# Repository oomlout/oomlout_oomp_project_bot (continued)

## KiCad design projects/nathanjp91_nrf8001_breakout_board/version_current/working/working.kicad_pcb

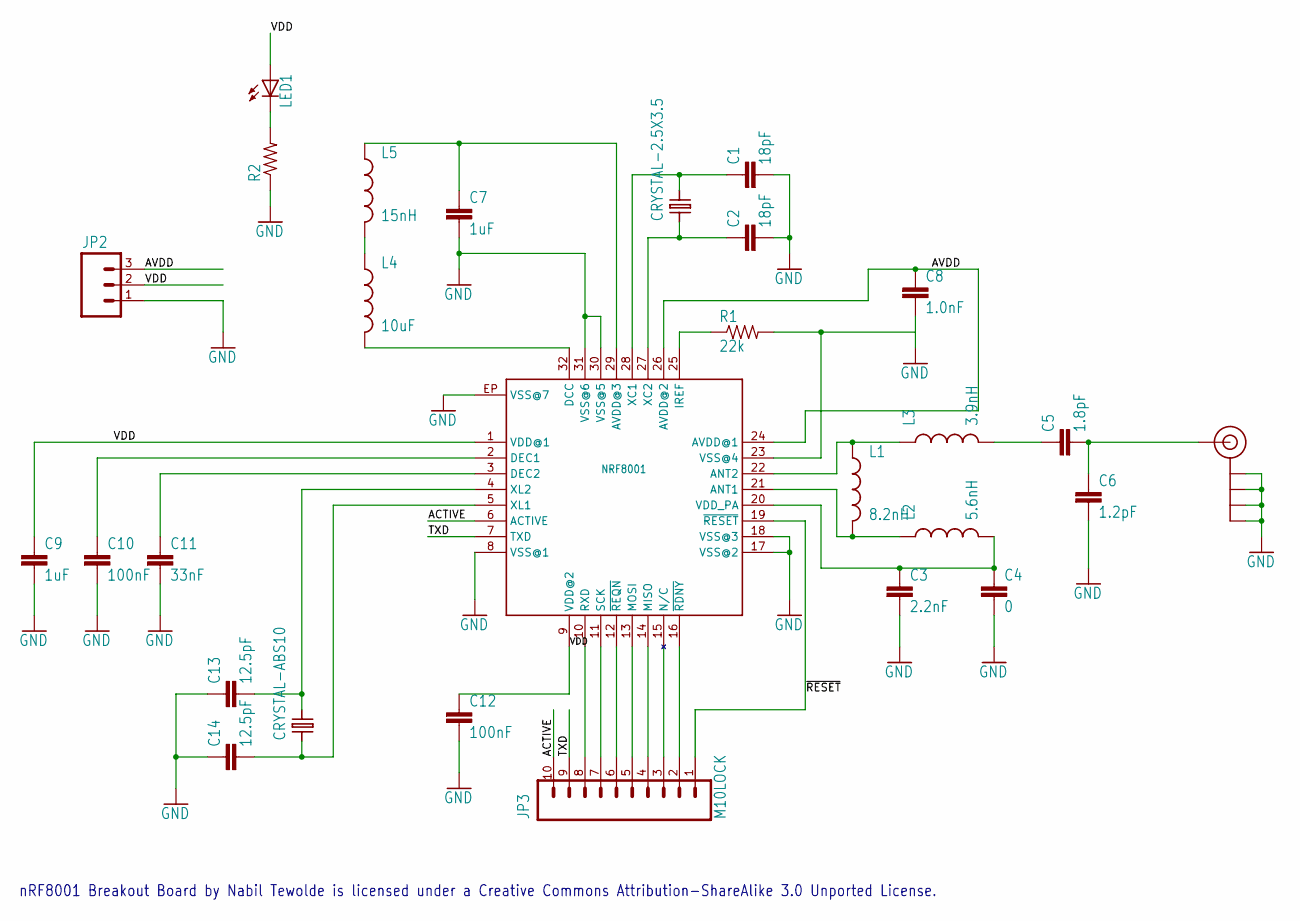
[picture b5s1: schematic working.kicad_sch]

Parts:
C1, C2: 18pF; 0603-CAP
C3: 2.2nF; 0603-CAP
C4: 0; 0603-CAP
C5: 1.8pF; 0603-CAP
C6: 1.2pF; 0603-CAP
C7, C9: 1uF; 0603-CAP
C8: 1.0nF; 0603-CAP
C10, C12: 100nF; 0603-CAP
C11: 33nF; 0603-CAP
C13, C14: 12.5pF; 0603-CAP
J$1: SMA_EDGE; SMA-EDGE
JP2: M03LOCK; 1X03_LOCK
JP3: M10LOCK; 1X10_LOCK
L1: 8.2nH; 0603
L2: 5.6nH; 0603
L3: 3.9nH; 0603
L4: 10uF; 0603
L5: 15nH; 0603
LED1: LED0603; LED-0603
R1: 22k; 0603-RES
R2: RESISTOR0603-RES; 0603-RES
U1: NRF8001; QFN-32
X1: CRYSTAL-2.5X3.5
X2: CRYSTAL-ABS10

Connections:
ACTIVE: JP3.10, U1.6 (ACTIVE)
AVDD: C8.1, JP2.3, U1.24 (AVDD@1), U1.26 (AVDD@2)
unnamed: L4.1, L5.2
unnamed: L4.2, U1.32 (DCC)
unnamed: L1.1, L3.1, U1.22 (ANT2)
unnamed: C7.1, L5.1, U1.29 (AVDD@3)
unnamed: LED1.C, R2.2
unnamed: C10.1, U1.2 (DEC1)
unnamed: C11.1, U1.3 (DEC2)
unnamed: L1.2, L2.1, U1.21 (ANT1)
unnamed: C5.1, L3.2
unnamed: C5.2, C6.1, J$1.SIG (SIGNAL)
unnamed: R1.1, U1.25 (IREF)
unnamed: C3.1, C4.1, L2.2, U1.20 (VDD_PA)
unnamed: C2.1, U1.27 (XC2), X1.P$1
unnamed: C1.1, U1.28 (XC1), X1.P$3
unnamed: C13.2, U1.4 (XL2), X2.P$2
unnamed: C14.2, U1.5 (XL1), X2.P$1
unnamed: JP3.2, U1.16 (~RDNY)
unnamed: JP3.3, U1.15 (N/C)
unnamed: JP3.4, U1.14 (MISO)
unnamed: JP3.5, U1.13 (MOSI)
unnamed: JP3.6, U1.12 (~REQN)
unnamed: JP3.7, U1.11 (SCK)
unnamed: JP3.8, U1.10 (RXD)
TXD: JP3.9, U1.7 (TXD)
VDD: C9.1, C12.1, JP2.2, LED1.A, U1.1 (VDD@1), U1.9 (VDD@2)
~RESET: JP3.1, U1.19 (~RESET)

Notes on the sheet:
nRF8001 Breakout Board by Nabil Tewolde is licensed under a Creative Commons Attribution-ShareAlike 3.0 Unported License.

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
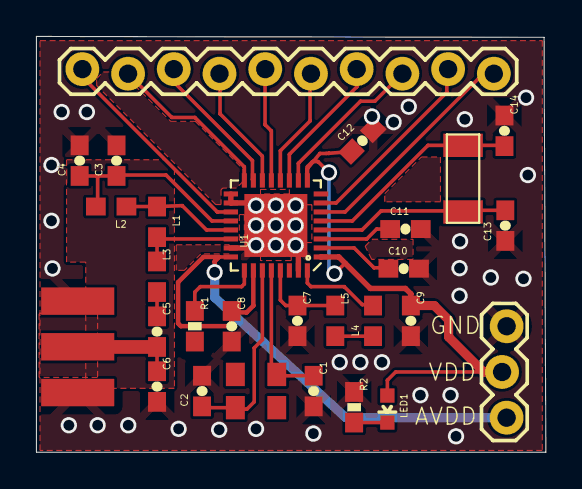
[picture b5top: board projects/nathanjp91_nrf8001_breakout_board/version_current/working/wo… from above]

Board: 2 copper layers, 28.3 x 23.1 mm, 28 parts (0 on the bottom side), 29 nets.

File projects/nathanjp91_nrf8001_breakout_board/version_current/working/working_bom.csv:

"Id";"Designator";"Footprint";"Quantity";"Designation";"Supplier and ref";
1;"C14,C13";"0603-CAP";2;"12.5pF";;;
2;"C3";"0603-CAP";1;"2.2nF";;;
3;"L4";"0603";1;"10uF";;;
4;"C6";"0603-CAP";1;"1.2pF";;;
5;"J$1";"SMA-EDGE";1;"SMA_EDGE";;;
6;"C12,C10";"0603-CAP";2;"100nF";;;
7;"L3";"0603";1;"3.9nH";;;
8;"JP3";"1X10_LOCK";1;"M10LOCK";;;
9;"C4";"0603-CAP";1;"0";;;
10;"U1";"QFN-32";1;"NRF8001";;;
11;"L1";"0603";1;"8.2nH";;;
12;"C5";"0603-CAP";1;"1.8pF";;;
13;"X1";"CRYSTAL-2.5X3.5";1;"16MHz";;;
14;"C8";"0603-CAP";1;"1.0nF";;;
15;"C7,C9";"0603-CAP";2;"1uF";;;
16;"X2";"CRYSTAL-ABS10";1;"32.768kHz";;;
17;"C2,C1";"0603-CAP";2;"18pF";;;
18;"L2";"0603";1;"5.6nH";;;
19;"C11";"0603-CAP";1;"33nF";;;
20;"LED1";"LED-0603";1;"";;;
21;"L5";"0603";1;"15nH";;;
22;"R2";"0603-RES";1;"";;;
23;"R1";"0603-RES";1;"22k";;;
24;"JP2";"1X03_LOCK";1;"";;;

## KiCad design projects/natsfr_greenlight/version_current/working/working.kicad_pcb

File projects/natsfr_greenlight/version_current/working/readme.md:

# Greenlight by natsfr  
This is a harvested standardized copy of a project from github.  
The original project can be found at:  
https://github.com/natsfr/Greenlight  
Please consult that link for additional, details, files, and license information.  
Note: It was auto harvested and if the original repo had more than one board file or anything out of the ordinary the files here are likely not representative.

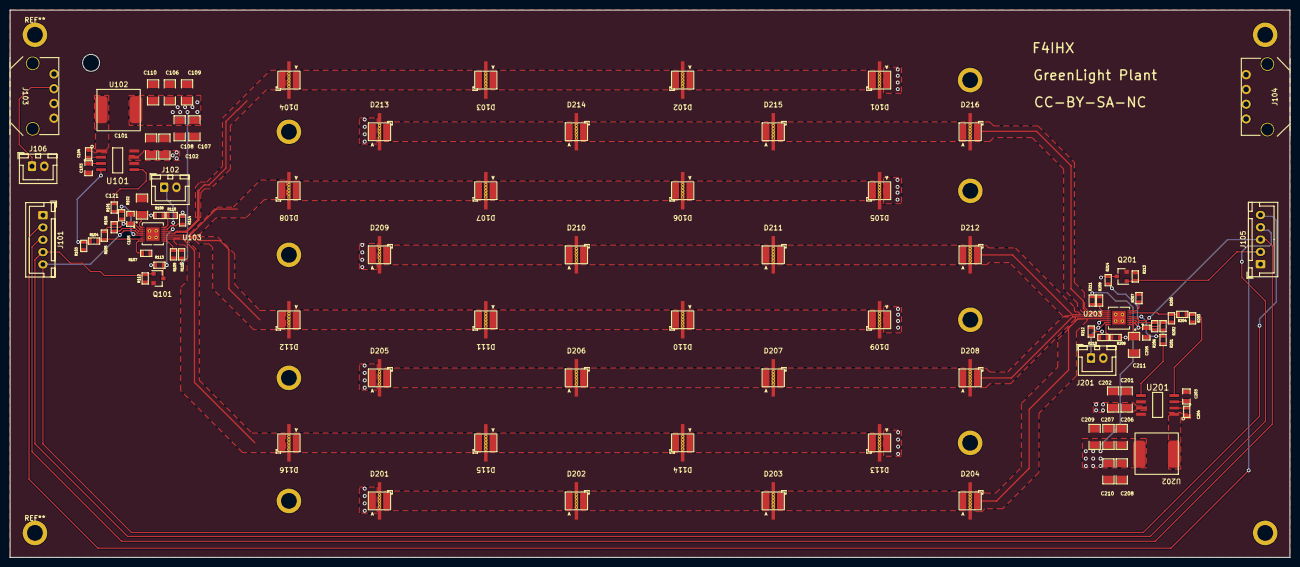
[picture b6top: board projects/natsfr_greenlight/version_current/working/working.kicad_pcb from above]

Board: 4 copper layers, 260.0 x 111.2 mm, 97 parts (0 on the bottom side), 68 nets.

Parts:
C101, C102, C121, C201, C202, C211: 4.7uF; SM1206
C103, C105, C203, C205: 1uF; SM0805
C104, C204: 100nF; SM0603
C106, C107, C108, C109, C110, C206, C207, C208, C209, C210: 10uF; SM1206
D101, D102, D103, D104, D105, D106, D107, D108, D109, D110, D111, D112, D113, D114, D115, D116, D202, D203, D204, D206, D207, D208, D210, D211, D212, D214, D215, D216: LED_TPAD; XLamp_MLE
D201, D205, D209, D213: NC; XLamp_MLE
J101, J105: Conn_01x05; JST_XH_B5B-XH-A_1x05_P2.50mm_Vertical
J102, J201: NTC; JST_XH_B2B-XH-A_1x02_P2.50mm_Vertical
J103, J104: Conn_01x04; MICROFIT_4POS_FEM_43650-0403
J106: FAN Connector; JST_XH_B2B-XH-A_1x02_P2.50mm_Vertical
Q101, Q201: BSS138; SOT-23
R101, R110, R201, R210: 0; SM0603
R102, R103, R112, R113, R202, R203, R213, R214: 10k; SM0603
R104, R204: 5k; SM0603
R105, R205: 15k; SM0603
R106, R206: 52.3k; SM0603
R107, R207: 7.32k; SM0603
R108, R114, R208, R212: NC; SM0603
R109, R111, R209, R211: TBD; SM0603
U101, U201: L6982; SOIC-8_208mil
U102, U202: 22uH; IND_SRP8540A_8.1x8.4x3.8mm
U103, U203: ADP8140ACPZ; ADP8140_LFCSP16_4x4_0.4mm

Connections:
+24V: C101.1, C102.1, C121.1, C201.1, C202.1, C211.1, J103.3, J103.4, J104.3, J104.4, J106.1, R108.2, R114.2, R208.2, R212.2, U101.7 (VIN), U103.1 (Vin), U201.7 (VIN), U203.1 (Vin)
/BLUE_PWM: J101.2, J105.2, Q201.1 (G), R213.2
/Blue LEDS/R01: D201.K, D202.A
/Blue LEDS/R02: D202.K, D203.A
/Blue LEDS/R03: D203.K, D204.A
/Blue LEDS/R04: D204.K, U203.13 (SINK1)
/Blue LEDS/R11: D205.K, D206.A
/Blue LEDS/R12: D206.K, D207.A
/Blue LEDS/R13: D207.K, D208.A
/Blue LEDS/R14: D208.K, U203.12 (SINK2)
/Blue LEDS/R21: D209.K, D210.A
/Blue LEDS/R22: D210.K, D211.A
/Blue LEDS/R23: D211.K, D212.A
/Blue LEDS/R24: D212.K, U203.11 (SINK3)
/Blue LEDS/R31: D213.K, D214.A
/Blue LEDS/R32: D214.K, D215.A
/Blue LEDS/R33: D215.K, D216.A
/Blue LEDS/R34: D216.K, U203.10 (SINK4)
/Blue LEDS/RED_FB: R203.1, R204.1, U201.4 (FB)
/Blue LEDS/RSW: C204.1, U201.1 (SW), U202.1
/Blue LEDS/VREG_RED: C205.1, R202.2, R205.1, R214.2, U203.2 (REG)
/Blue LEDS/VRed: C206.1, C207.1, C208.1, C209.1, C210.1, D201.A, D205.A, D209.A, D213.A, R211.1, U202.2
/EN_BLUE: J101.3, J105.3, U203.4 (EN)
/EN_RED: J101.5, J105.5, U103.4 (EN)
/R01: D101.K, D102.A
/R02: D102.K, D103.A
/R03: D103.K, D104.A
/R04: D104.K, U103.13 (SINK1)
/R11: D105.K, D106.A
/R12: D106.K, D107.A
/R13: D107.K, D108.A
/R14: D108.K, U103.12 (SINK2)
/R21: D109.K, D110.A
/R22: D110.K, D111.A
/R23: D111.K, D112.A
/R24: D112.K, U103.11 (SINK3)
/R31: D113.K, D114.A
/R32: D114.K, D115.A
/R33: D115.K, D116.A
/R34: D116.K, U103.10 (SINK4)
/RED_FB: R103.1, R104.1, U101.4 (FB)
/RED_PWM: J101.4, J105.4, Q101.1 (G), R112.2
/RSW: C104.1, U101.1 (SW), U102.1
/VREG_RED: C105.1, R102.2, R105.1, R113.2, U103.2 (REG)
/VRed: C106.1, C107.1, C108.1, C109.1, C110.1, D101.A, D105.A, D109.A, D113.A, R111.1, U102.2
GND: C101.2, C102.2, C103.2, C105.2, C106.2, C107.2, C108.2, C109.2, C110.2, C121.2, C201.2, C202.2, C203.2, C205.2, C206.2, C207.2, C208.2, C209.2, C210.2, C211.2, D101.N (PAD), D102.N (PAD), D103.N (PAD), D104.N (PAD), D105.N (PAD), D106.N (PAD), D107.N (PAD), D108.N (PAD), D109.N (PAD), D110.N (PAD), D111.N (PAD), D112.N (PAD), D113.N (PAD), D114.N (PAD), D115.N (PAD), D116.N (PAD), D201.N (PAD), D202.N (PAD), D203.N (PAD), D204.N (PAD), D205.N (PAD), D206.N (PAD), D207.N (PAD), D208.N (PAD), D209.N (PAD), D210.N (PAD), D211.N (PAD), D212.N (PAD), D213.N (PAD), D214.N (PAD), D215.N (PAD), D216.N (PAD), J101.1, J102.2, J103.1, J103.2, J104.1, J104.2, J105.1, J106.2, J201.2, Q101.2 (S), Q201.2 (S), R103.2, R106.2, R107.2, R109.2, R110.2, R112.1, R203.2, R206.2, R207.2, R209.2, R210.2, R213.1, U101.6 (AGND), U101.8 (PGND), U103.17 (EPAD), U201.6 (AGND), U201.8 (PGND), U203.17 (EPAD)
unnamed: C103.1, U101.3 (VCC)
unnamed: C104.2, U101.2 (BOOT)
unnamed: C203.1, U201.3 (VCC)
unnamed: C204.2, U201.2 (BOOT)
unnamed: J102.1, R114.1, U103.15 (VT)
unnamed: J201.1, R212.1, U203.15 (VT)
unnamed: Q101.3 (D), R113.1, U103.14 (DIM)
unnamed: Q201.3 (D), R214.1, U203.14 (DIM)
unnamed: R101.1, R102.1, U103.5 (~FAULT)
unnamed: R101.2, U101.5 (EN/CLKIN)
unnamed: R104.2, R105.2, U103.7 (COMP)
unnamed: R106.1, U103.3 (MODE)
unnamed: R107.1, U103.8 (ISET)
unnamed: R108.1, R110.1, U103.16 (MIN)
unnamed: R109.1, R111.2, U103.9 (VO_SNS)
unnamed: R201.1, R202.1, U203.5 (~FAULT)
unnamed: R201.2, U201.5 (EN/CLKIN)
unnamed: R204.2, R205.2, U203.7 (COMP)
unnamed: R206.1, U203.3 (MODE)
unnamed: R207.1, U203.8 (ISET)
unnamed: R208.1, R210.1, U203.16 (MIN)
unnamed: R209.1, R211.2, U203.9 (VO_SNS)

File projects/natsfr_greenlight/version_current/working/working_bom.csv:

"Id";"Designator";"Footprint";"Quantity";"Designation";"Supplier and ref";
1;"D109,D104,D106,D114,D107,D208,D203,D113,D210,D111,D212,D112,D206,D102,D103,D207,D115,D204,D108,D116,D211,D110,D101,D216,D214,D215,D202,D105";"XLamp_MLE";28;"LED_TPAD";;;
2;"J104,J103";"MICROFIT_4POS_FEM_43650-0403";2;"Conn_01x04";;;
3;"C207,C107,C206,C110,C106,C109,C108,C210,C208,C209";"SM1206";10;"10uF";;;
4;"R203,R214,R213,R103,R113,R202,R102,R112";"SM0603";8;"10k";;;
5;"U202,U102";"IND_SRP8540A_8.1x8.4x3.8mm";2;"22uH";;;
6;"R204,R104";"SM0603";2;"5k";;;
7;"R208,R114,R108,R212";"SM0603";4;"NC";;;
8;"R109,R111,R209,R211";"SM0603";4;"TBD";;;
9;"REF**,REF**,REF**,REF**,REF**,REF**,REF**,REF**,REF**,REF**,REF**,REF**";"3.2mm_plated";12;"3.2mm_plated";;;
10;"Q101,Q201";"SOT-23";2;"BSS138";;;
11;"U103,U203";"ADP8140_LFCSP16_4x4_0.4mm";2;"ADP8140ACPZ";;;
12;"J106";"JST_XH_B2B-XH-A_1x02_P2.50mm_Vertical";1;"FAN Connector";;;
13;"C211,C201,C202,C121,C101,C102";"SM1206";6;"4.7uF";;;
14;"D205,D201,D209,D213";"XLamp_MLE";4;"NC";;;
15;"U201,U101";"SOIC-8_208mil";2;"L6982";;;
16;"C204,C104";"SM0603";2;"100nF";;;
17;"R206,R106";"SM0603";2;"52.3k";;;
18;"R105,R205";"SM0603";2;"15k";;;
19;"C103,C105,C203,C205";"SM0805";4;"1uF";;;
20;"R107,R207";"SM0603";2;"7.32k";;;
21;"R101,R110,R201,R210";"SM0603";4;"0";;;
22;"J101,J105";"JST_XH_B5B-XH-A_1x05_P2.50mm_Vertical";2;"Conn_01x05";;;
23;"REF**";"3.45MM_NOTPLATED";1;"3.45MM_NOTPLATED";;;
24;"J201,J102";"JST_XH_B2B-XH-A_1x02_P2.50mm_Vertical";2;"NTC";;;
